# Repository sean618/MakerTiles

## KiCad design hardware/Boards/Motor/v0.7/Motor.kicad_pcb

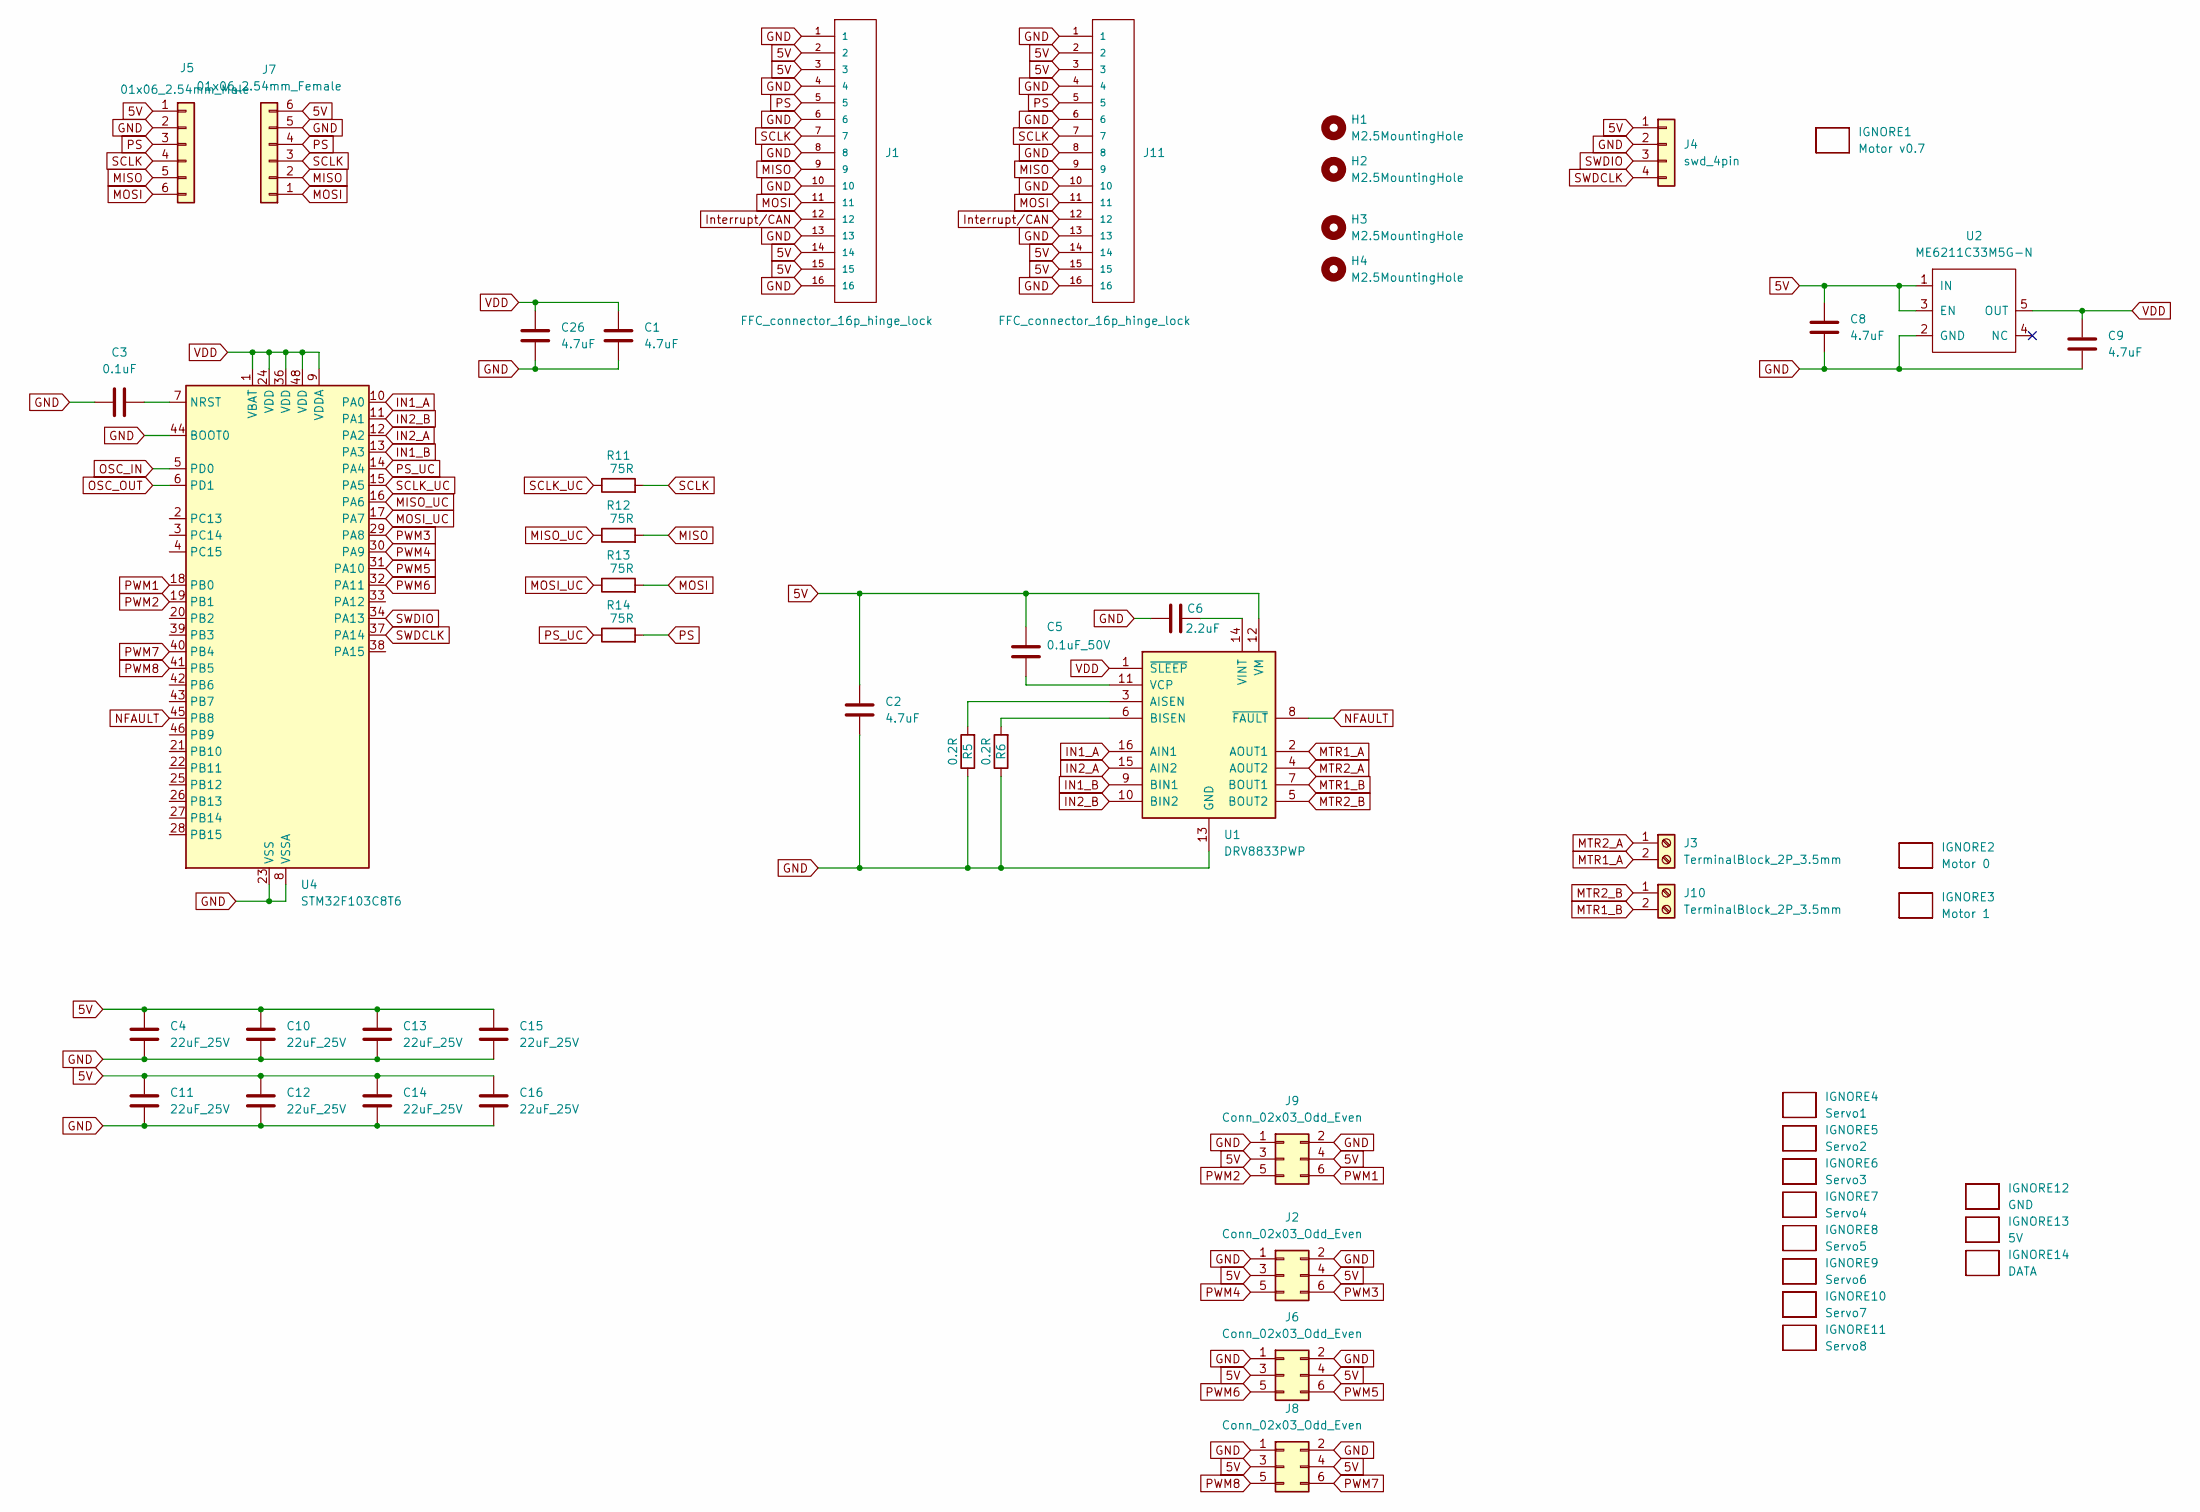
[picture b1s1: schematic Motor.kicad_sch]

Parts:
C1, C2, C8, C9, C26: 4.7uF; C_0402_1005Metric
C3: 0.1uF; C_0402_1005Metric
C4, C10, C11, C12, C13, C14, C15, C16: 22uF_25V; C_0805_2012Metric
C5: 0.1uF_50V; C_0402_1005Metric
C6: 2.2uF; C_0402_1005Metric
H1, H2, H3, H4: M2.5MountingHole; MountingHole_2.7mm_M2.5_ISO7380
IGNORE1: Motor v0.7; BoardText
IGNORE2: Motor 0; BoardText
IGNORE3: Motor 1; BoardText
IGNORE4: Servo1; BoardText
IGNORE5: Servo2; BoardText
IGNORE6: Servo3; BoardText
IGNORE7: Servo4; BoardText
IGNORE8: Servo5; BoardText
IGNORE9: Servo6; BoardText
IGNORE10: Servo7; BoardText
IGNORE11: Servo8; BoardText
IGNORE12: GND; BoardText
IGNORE13: 5V; BoardText
IGNORE14: DATA; BoardText
J1, J11: FFC_connector_16p_hinge_lock
J2, J6, J8, J9: Conn_02x03_Odd_Even; PinHeader_2x03_P2.54mm_Vertical_SMD
J3, J10: TerminalBlock_2P_3.5mm
J4: swd_4pin; swd_header
J5: 01x06_2.54mm_Male
J7: 01x06_2.54mm_Female
R5, R6: 0.2R; R_1210_3225Metric
R11, R12, R13, R14: 75R; R_0402_1005Metric
U1: DRV8833PWP; HTSSOP-16-1EP_4.4x5mm_P0.65mm_EP3.4x5mm_Mask2.46x2.31mm_The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
U2: ME6211C33M5G-N; SOT-23-5
U4: STM32F103C8T6; LQFP-48_7x7mm_P0.5mm

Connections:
5V: C2.1, C4.1, C5.1, C8.1, C10.1, C11.1, C12.1, C13.1, C14.1, C15.1, C16.1, J1.2, J1.3, J1.14, J1.15, J2.3, J2.4, J4.1, J5.1, J6.3, J6.4, J7.6, J8.3, J8.4, J9.3, J9.4, J11.2, J11.3, J11.14, J11.15, U1.12 (VM), U2.1 (IN), U2.3 (EN)
GND: C1.2, C2.2, C3.1, C4.2, C6.1, C8.2, C9.2, C10.2, C11.2, C12.2, C13.2, C14.2, C15.2, C16.2, C26.2, J1.1, J1.4, J1.6, J1.8, J1.10, J1.13, J1.16, J2.1, J2.2, J4.2, J5.2, J6.1, J6.2, J7.5, J8.1, J8.2, J9.1, J9.2, J11.1, J11.4, J11.6, J11.8, J11.10, J11.13, J11.16, R5.1, R6.1, U1.13 (GND), U1.17 (GND), U2.2 (GND), U4.8 (VSSA), U4.23 (VSS), U4.35 (VSS), U4.44 (BOOT0), U4.47 (VSS)
IN1_A: U1.16 (AIN1), U4.10 (PA0)
IN1_B: U1.9 (BIN1), U4.13 (PA3)
IN2_A: U1.15 (AIN2), U4.12 (PA2)
IN2_B: U1.10 (BIN2), U4.11 (PA1)
Interrupt/CAN: J1.12, J11.12
MISO: J1.9, J5.5, J7.2, J11.9, R12.2
MISO_UC: R12.1, U4.16 (PA6)
MOSI: J1.11, J5.6, J7.1, J11.11, R13.2
MOSI_UC: R13.1, U4.17 (PA7)
MTR1_A: J3.2, U1.2 (AOUT1)
MTR1_B: J10.2, U1.7 (BOUT1)
MTR2_A: J3.1, U1.4 (AOUT2)
MTR2_B: J10.1, U1.5 (BOUT2)
NFAULT: U1.8 (~FAULT), U4.45 (PB8)
unnamed: R5.2, U1.3 (AISEN)
unnamed: R6.2, U1.6 (BISEN)
unnamed: C5.2, U1.11 (VCP)
unnamed: C6.2, U1.14 (VINT)
unnamed: C3.2, U4.7 (NRST)
OSC_IN: U4.5 (PD0)
OSC_OUT: U4.6 (PD1)
PS: J1.5, J5.3, J7.4, J11.5, R14.2
PS_UC: R14.1, U4.14 (PA4)
PWM1: J9.6, U4.18 (PB0)
PWM2: J9.5, U4.19 (PB1)
PWM3: J2.6, U4.29 (PA8)
PWM4: J2.5, U4.30 (PA9)
PWM5: J6.6, U4.31 (PA10)
PWM6: J6.5, U4.32 (PA11)
PWM7: J8.6, U4.40 (PB4)
PWM8: J8.5, U4.41 (PB5)
SCLK: J1.7, J5.4, J7.3, J11.7, R11.2
SCLK_UC: R11.1, U4.15 (PA5)
SWDCLK: J4.4, U4.37 (PA14)
SWDIO: J4.3, U4.34 (PA13)
VDD: C1.1, C9.1, C26.1, U1.1 (~SLEEP), U2.5 (OUT), U4.1 (VBAT), U4.9 (VDDA), U4.24 (VDD), U4.36 (VDD), U4.48 (VDD)

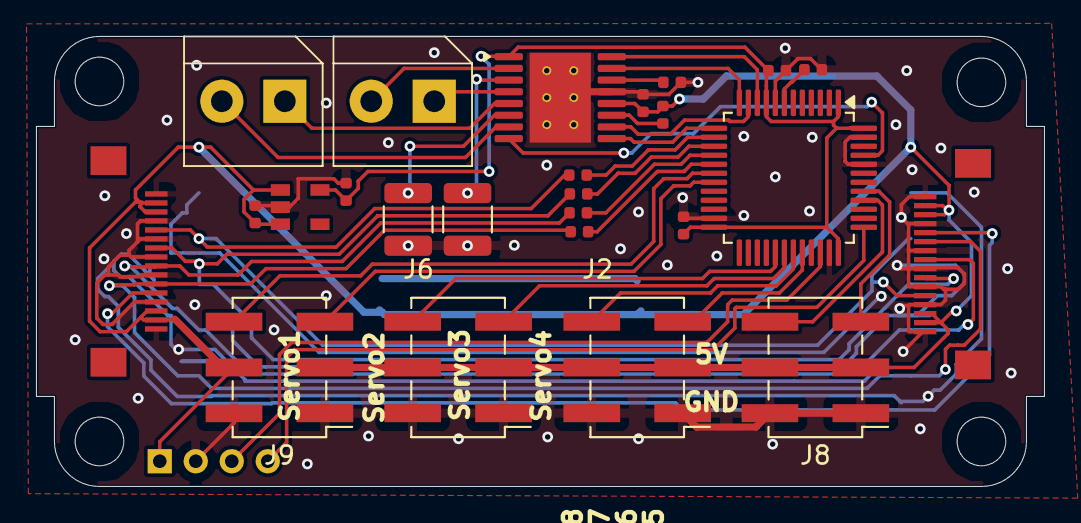
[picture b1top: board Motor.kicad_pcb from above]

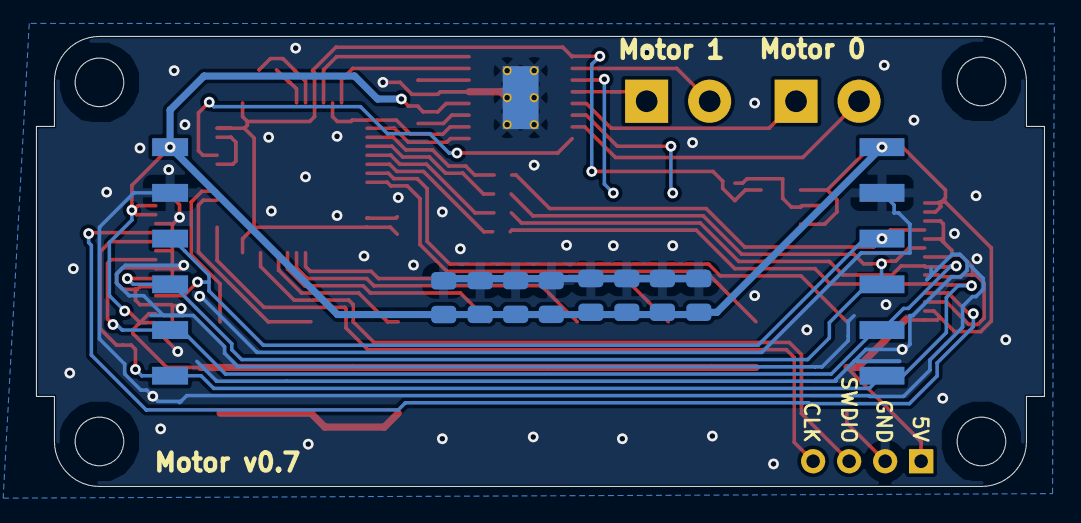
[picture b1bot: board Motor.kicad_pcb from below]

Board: 2 copper layers, 56.0 x 25.0 mm, 54 parts (21 on the bottom side), 36 nets.

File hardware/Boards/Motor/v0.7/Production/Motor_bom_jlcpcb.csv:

Comment,Designator,Footprint,LCSC Part Number
4.7uF,"C9,C1,C2,C26,C8",C_0402_1005Metric,C23733
DRV8833PWP,U1,HTSSOP-16-1EP_4.4x5mm_P0.65mm_EP3.4x5mm_Mask2.46x2.31mm_ThermalVias,C50506
FFC_connector_16p_hinge_lock,"J1,J11",FFC_connector_16p_hinge_lock,C262665
Conn_02x03_Odd_Even,"J2,J8,J6,J9",PinHeader_2x03_P2.54mm_Vertical_SMD,C22438447
0.1uF_50V,C5,C_0402_1005Metric,C77020
75R,"R13,R14,R12,R11",R_0402_1005Metric,C25133
TerminalBlock_2P_3.5mm,"J3,J10",TerminalBlock_2P_3.5mm,C466970
ME6211C33M5G-N,U2,SOT-23-5,C81233
0.1uF,C3,C_0402_1005Metric,C1525
STM32F103C8T6,U4,LQFP-48_7x7mm_P0.5mm,C8734
2.2uF,C6,C_0402_1005Metric,C12530
0.2R,"R5,R6",R_1210_3225Metric,C52362
01x06_2.54mm_Male,J5,01x06_2.54mm_Male,C5242199
22uF_25V,"C15,C10,C12,C4,C14,C13,C11,C16",C_0805_2012Metric,C602037
01x06_2.54mm_Female,J7,01x06_2.54mm_Female,C5142239

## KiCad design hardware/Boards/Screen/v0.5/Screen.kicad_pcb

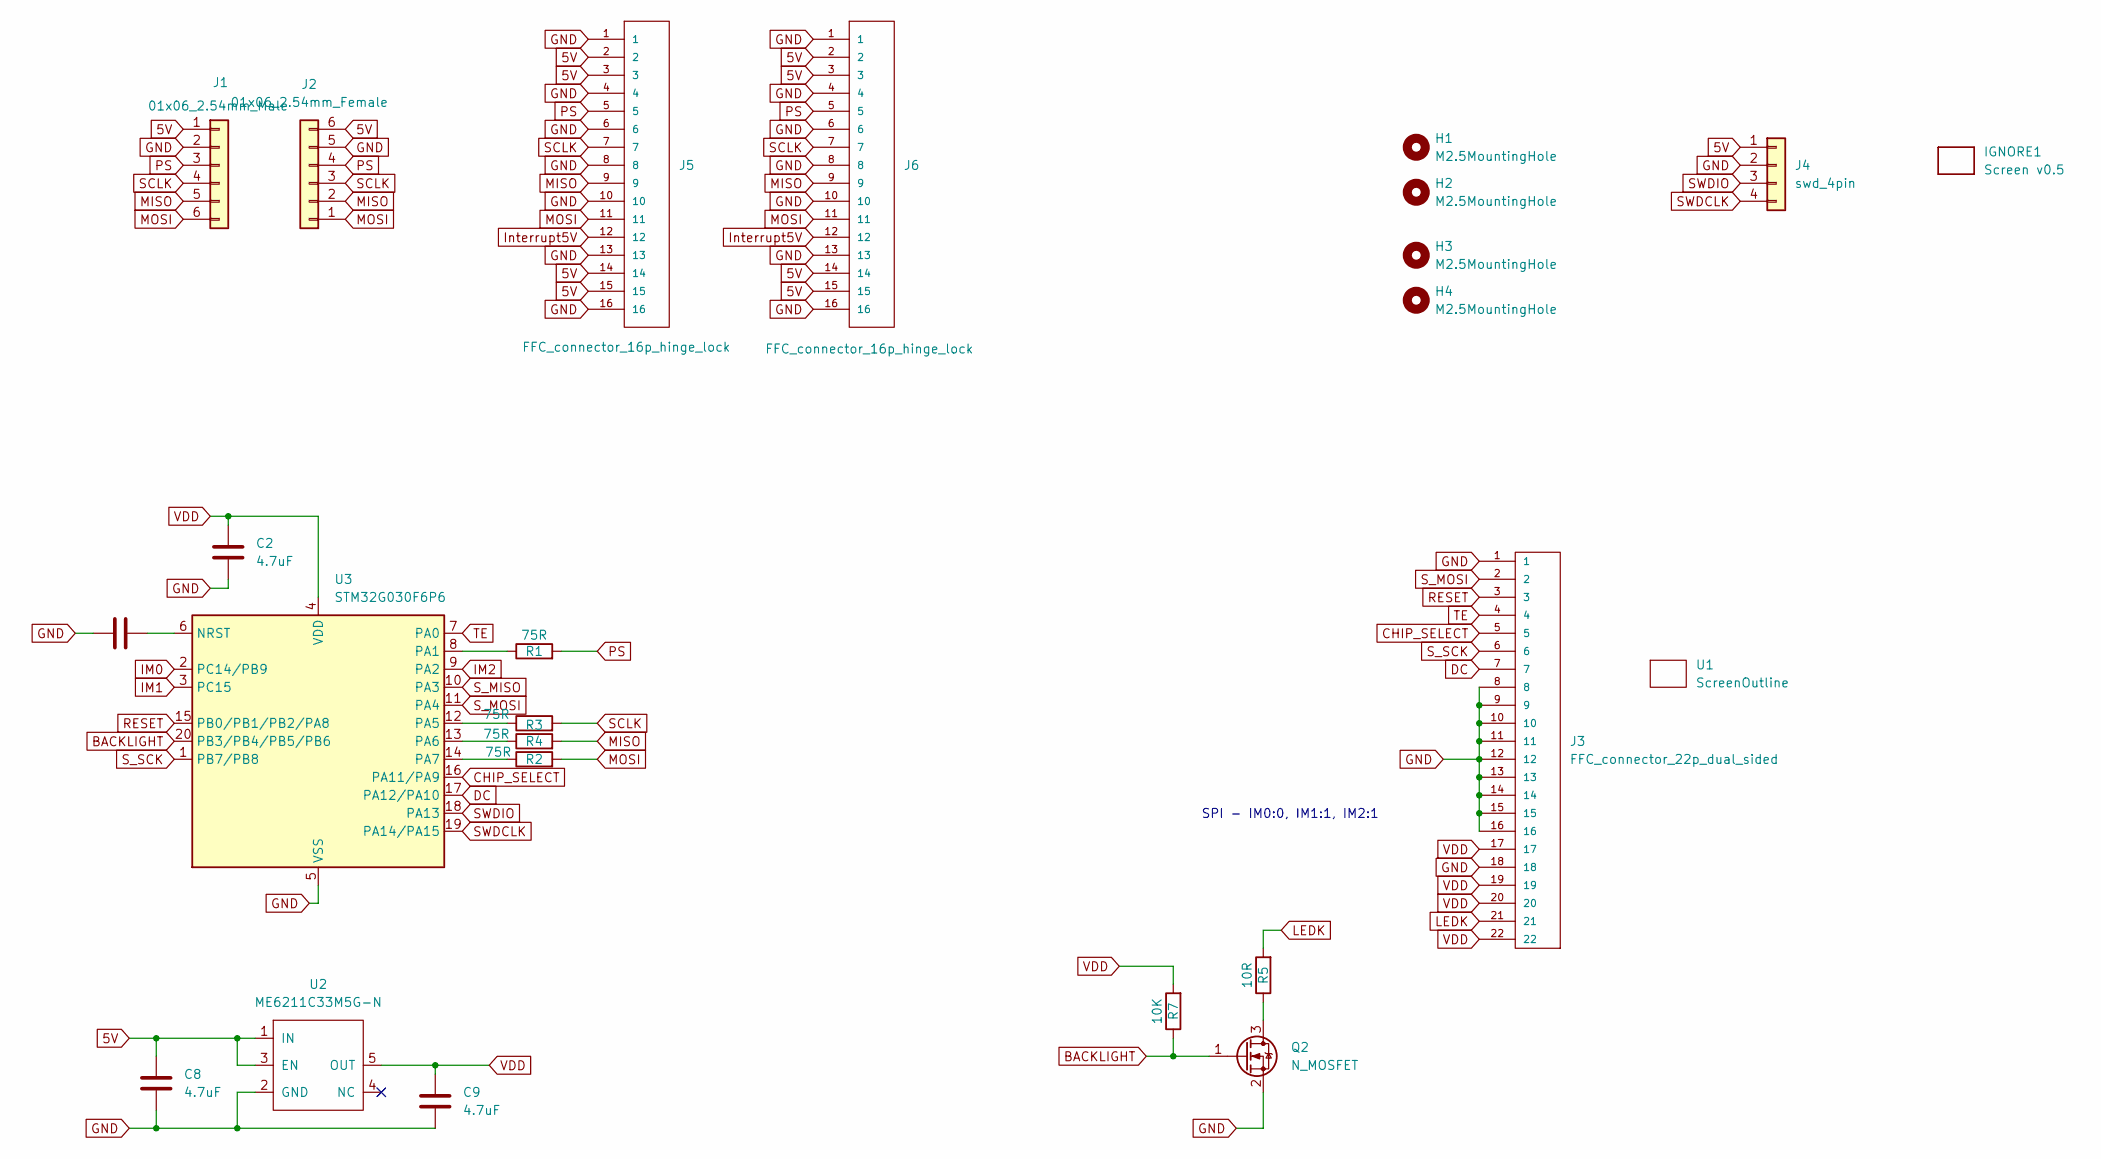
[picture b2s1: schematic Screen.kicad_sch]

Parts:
C1: 0.1uF; C_0402_1005Metric
C2, C8, C9: 4.7uF; C_0402_1005Metric
H1, H2, H3, H4: M2.5MountingHole; MountingHole_2.7mm_M2.5_ISO7380
IGNORE1: Screen v0.5; BoardText
J1: 01x06_2.54mm_Male
J2: 01x06_2.54mm_Female
J3: FFC_connector_22p_dual_sided; FFC_connector_22p_hinge_lock
J4: swd_4pin; swd_header
J5, J6: FFC_connector_16p_hinge_lock
Q2: N_MOSFET; SOT-23
R1, R2, R3, R4: 75R; R_0402_1005Metric
R5: 10R; R_0402_1005Metric
R7: 10K; R_0402_1005Metric
U1: ScreenOutline; 2InchScreen
U2: ME6211C33M5G-N; SOT-23-5
U3: STM32G030F6P6; TSSOP-20_4.4x6.5mm_P0.65mm

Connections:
5V: C8.1, J1.1, J2.6, J4.1, J5.2, J5.3, J5.14, J5.15, J6.2, J6.3, J6.14, J6.15, U2.1 (IN), U2.3 (EN)
BACKLIGHT: Q2.1 (G), R7.1, U3.20 (PB3/PB4/PB5/PB6)
CHIP_SELECT: J3.5, U3.16 (PA11/PA9)
DC: J3.7, U3.17 (PA12/PA10)
GND: C1.2, C2.2, C8.2, C9.2, J1.2, J2.5, J3.1, J3.8, J3.9, J3.10, J3.11, J3.12, J3.13, J3.14, J3.15, J3.16, J3.18, J4.2, J5.1, J5.4, J5.6, J5.8, J5.10, J5.13, J5.16, J6.1, J6.4, J6.6, J6.8, J6.10, J6.13, J6.16, Q2.2 (S), U2.2 (GND), U3.5 (VSS)
IM0: U3.2 (PC14/PB9)
IM1: U3.3 (PC15)
IM2: U3.9 (PA2)
Interrupt5V: J5.12, J6.12
LEDK: J3.21, R5.2
MISO: J1.5, J2.2, J5.9, J6.9, R4.2
MOSI: J1.6, J2.1, J5.11, J6.11, R2.2
unnamed: Q2.3 (D), R5.1
unnamed: C1.1, U3.6 (NRST)
unnamed: R1.1, U3.8 (PA1)
unnamed: R3.1, U3.12 (PA5)
unnamed: R4.1, U3.13 (PA6)
unnamed: R2.1, U3.14 (PA7)
PS: J1.3, J2.4, J5.5, J6.5, R1.2
RESET: J3.3, U3.15 (PB0/PB1/PB2/PA8)
SCLK: J1.4, J2.3, J5.7, J6.7, R3.2
SWDCLK: J4.4, U3.19 (PA14/PA15)
SWDIO: J4.3, U3.18 (PA13)
S_MISO: U3.10 (PA3)
S_MOSI: J3.2, U3.11 (PA4)
S_SCK: J3.6, U3.1 (PB7/PB8)
TE: J3.4, U3.7 (PA0)
VDD: C2.1, C9.1, J3.17, J3.19, J3.20, J3.22, R7.2, U2.5 (OUT), U3.4 (VDD)

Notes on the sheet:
SPI - IM0:0, IM1:1, IM2:1

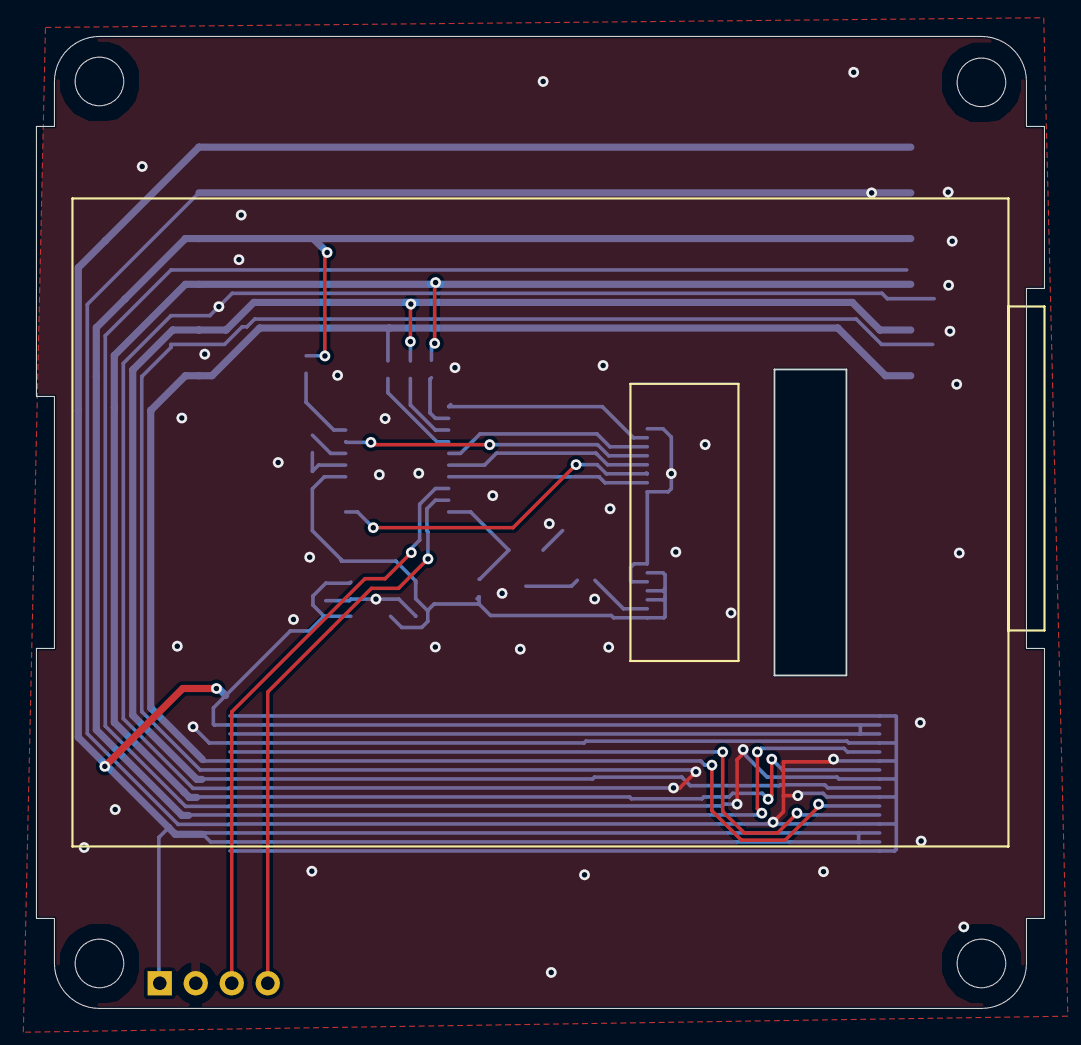
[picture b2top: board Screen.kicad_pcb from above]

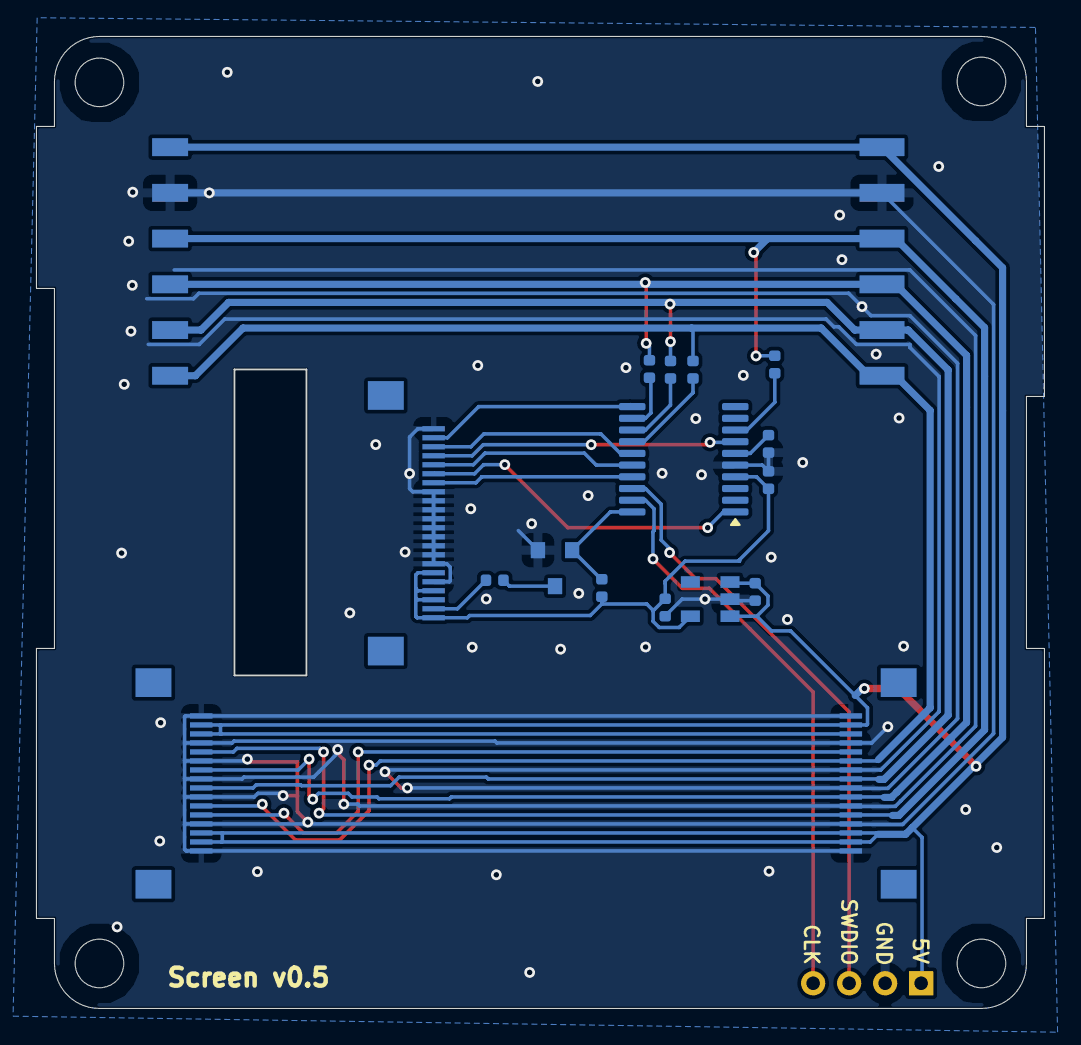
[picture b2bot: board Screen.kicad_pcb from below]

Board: 2 copper layers, 56.0 x 54.0 mm, 25 parts (18 on the bottom side), 24 nets.

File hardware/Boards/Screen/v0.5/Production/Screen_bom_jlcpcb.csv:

Comment,Designator,Footprint,LCSC Part Number
4.7uF,"C9,C8,C2",C_0402_1005Metric,C23733
FFC_connector_22p_dual_sided,J3,FFC_connector_22p_hinge_lock,C557729
FFC_connector_16p_hinge_lock,"J5,J6",FFC_connector_16p_hinge_lock,C262665
ME6211C33M5G-N,U2,SOT-23-5,C81233
75R,"R2,R3,R4,R1",R_0402_1005Metric,C25133
STM32G030F6P6,U3,TSSOP-20_4.4x6.5mm_P0.65mm,C529330
N_MOSFET,Q2,SOT-23,C8545
0.1uF,C1,C_0402_1005Metric,C1525
01x06_2.54mm_Female,J2,01x06_2.54mm_Female,C5142239
10R,R5,R_0402_1005Metric,C25077
01x06_2.54mm_Male,J1,01x06_2.54mm_Male,C5242199
10K,R7,R_0402_1005Metric,C25744

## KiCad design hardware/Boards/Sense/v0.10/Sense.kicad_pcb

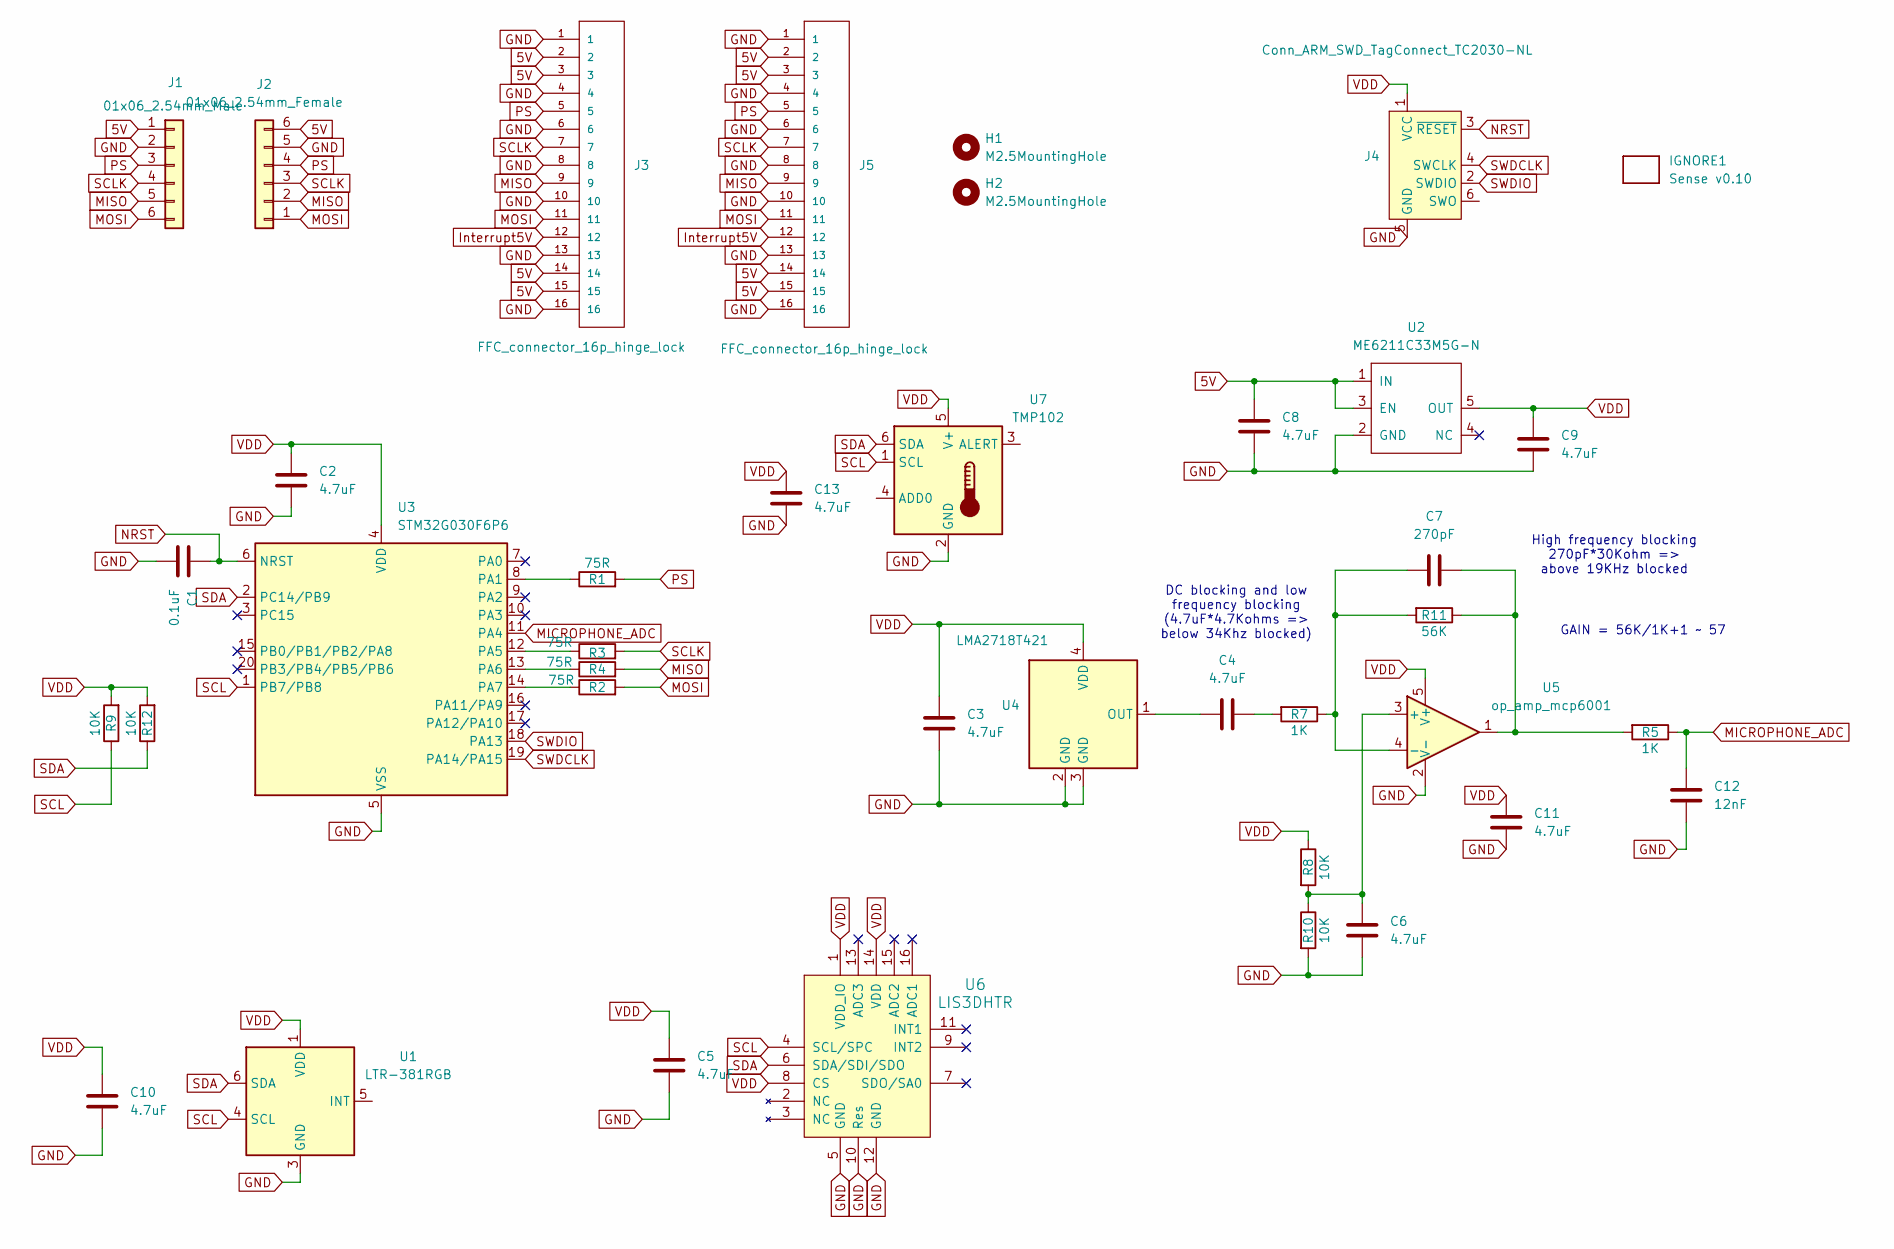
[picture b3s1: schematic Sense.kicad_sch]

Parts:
C1: 0.1uF; C_0402_1005Metric
C2, C3, C4, C5, C6, C8, C9, C10, C11, C13: 4.7uF; C_0402_1005Metric
C7: 270pF; C_0402_1005Metric
C12: 12nF; C_0402_1005Metric
H1, H2: M2.5MountingHole; MountingHole_2.7mm_M2.5_ISO7380
IGNORE1: Sense v0.10; BoardText
J1: 01x06_2.54mm_Male
J2: 01x06_2.54mm_Female
J3, J5: FFC_connector_16p_hinge_lock
J4: Conn_ARM_SWD_TagConnect_TC2030-NL; Tag-Connect_TC2030-IDC-NL_2x03_P1.27mm_Vertical
R1, R2, R3, R4: 75R; R_0402_1005Metric
R5, R7: 1K; R_0402_1005Metric
R8, R9, R10, R12: 10K; R_0402_1005Metric
R11: 56K; R_0402_1005Metric
U1: LTR-381RGB
U2: ME6211C33M5G-N; SOT-23-5
U3: STM32G030F6P6; TSSOP-20_4.4x6.5mm_P0.65mm
U4: LMA2718T421; SMD-4P-2.8x1.9mm
U5: op_amp_mcp6001; SOT-23-5
U6: LIS3DHTR; LGA-16_3x3mm_P0.5mm_LayoutBorder3x5y; Manufacturer_Part_Number LIS3DHTR
U7: TMP102; SOT-563

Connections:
5V: C8.1, J1.1, J2.6, J3.2, J3.3, J3.14, J3.15, J5.2, J5.3, J5.14, J5.15, U2.1 (IN), U2.3 (EN)
GND: C1.2, C2.2, C3.2, C5.2, C6.1, C8.2, C9.2, C10.2, C11.2, C12.1, C13.2, J1.2, J2.5, J3.1, J3.4, J3.6, J3.8, J3.10, J3.13, J3.16, J4.5 (GND), J5.1, J5.4, J5.6, J5.8, J5.10, J5.13, J5.16, R10.2, U1.3 (GND), U2.2 (GND), U3.5 (VSS), U4.2 (GND), U4.3 (GND), U5.2 (V-), U6.5 (GND), U6.10 (Res), U6.12 (GND), U7.2 (GND)
Interrupt5V: J3.12, J5.12
MICROPHONE_ADC: C12.2, R5.1, U3.11 (PA4)
MISO: J1.5, J2.2, J3.9, J5.9, R4.2
MOSI: J1.6, J2.1, J3.11, J5.11, R2.2
NRST: C1.1, J4.3 (~RESET), U3.6 (NRST)
unnamed: C4.2, R7.2
unnamed: C7.2, R5.2, R11.1, U5.1
unnamed: R1.1, U3.8 (PA1)
unnamed: R3.1, U3.12 (PA5)
unnamed: R4.1, U3.13 (PA6)
unnamed: R2.1, U3.14 (PA7)
unnamed: C4.1, U4.1 (OUT)
unnamed: C6.2, R8.2, R10.1, U5.3 (+)
unnamed: C7.1, R7.1, R11.2, U5.4 (-)
PS: J1.3, J2.4, J3.5, J5.5, R1.2
SCL: R9.1, U1.4 (SCL), U3.1 (PB7/PB8), U6.4 (SCL/SPC), U7.1 (SCL)
SCLK: J1.4, J2.3, J3.7, J5.7, R3.2
SDA: R12.1, U1.6 (SDA), U3.2 (PC14/PB9), U6.6 (SDA/SDI/SDO), U7.6 (SDA)
SWDCLK: J4.4 (SWCLK), U3.19 (PA14/PA15)
SWDIO: J4.2 (SWDIO), U3.18 (PA13)
VDD: C2.1, C3.1, C5.1, C9.1, C10.1, C11.1, C13.1, J4.1 (VCC), R8.1, R9.2, R12.2, U1.1 (VDD), U2.5 (OUT), U3.4 (VDD), U4.4 (VDD), U5.5 (V+), U6.1 (VDD_IO), U6.8 (CS), U6.14 (VDD), U7.5 (V+)

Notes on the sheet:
GAIN = 56K/1K+1 ~ 57
High frequency blocking 270pF*30Kohm => above 19KHz blocked
DC blocking and low frequency blocking (4.7uF*4.7Kohms => below 34Khz blocked)

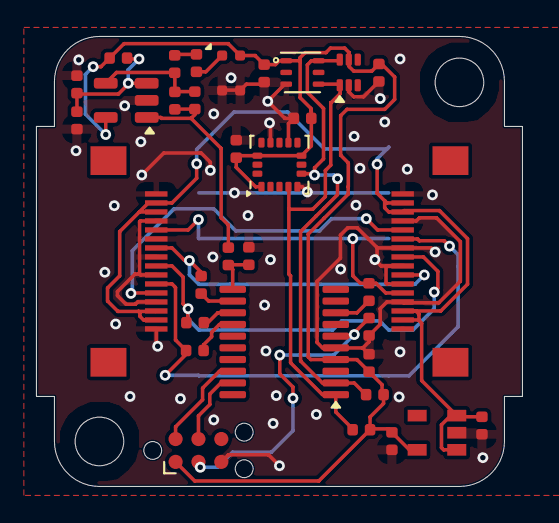
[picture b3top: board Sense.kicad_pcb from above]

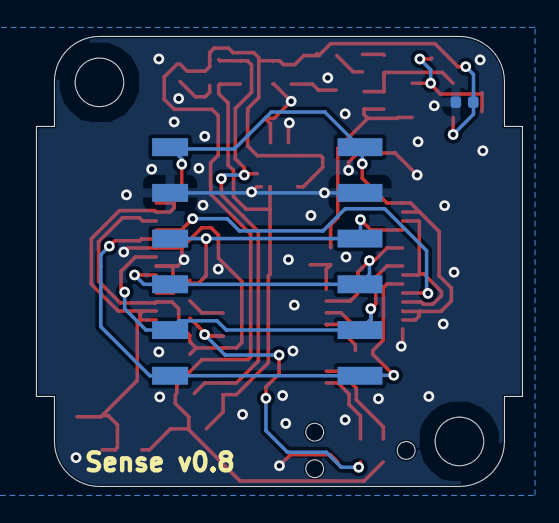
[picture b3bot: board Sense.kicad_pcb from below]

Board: 2 copper layers, 27.0 x 25.0 mm, 39 parts (3 on the bottom side), 23 nets.

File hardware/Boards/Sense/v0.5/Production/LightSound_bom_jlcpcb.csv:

Comment,Designator,Footprint,LCSC Part Number
4.7uF,"C9,C8,C2,C3",C_0402_1005Metric,C23733
FFC_connector_16p_hinge_lock,"J3,J5",FFC_connector_16p_hinge_lock,C262665
10K,"R5,R6",R_0402_1005Metric,C25744
ME6211C33M5G-N,U2,SOT-23-5,C81233
75R,"R2,R3,R4,R1",R_0402_1005Metric,C25133
STM32G030F6P6,U3,TSSOP-20_4.4x6.5mm_P0.65mm,C529330
WMM7027ATSN1-4/TR,U4,LGA-4,C2931973
0.1uF,C1,C_0402_1005Metric,C1525
LTR-381RGB,U1,LTR-381RGB,C2944020
01x06_2.54mm_Male,J1,01x06_2.54mm_Male,C5242199
01x06_2.54mm_Female,J2,01x06_2.54mm_Female,C5142239

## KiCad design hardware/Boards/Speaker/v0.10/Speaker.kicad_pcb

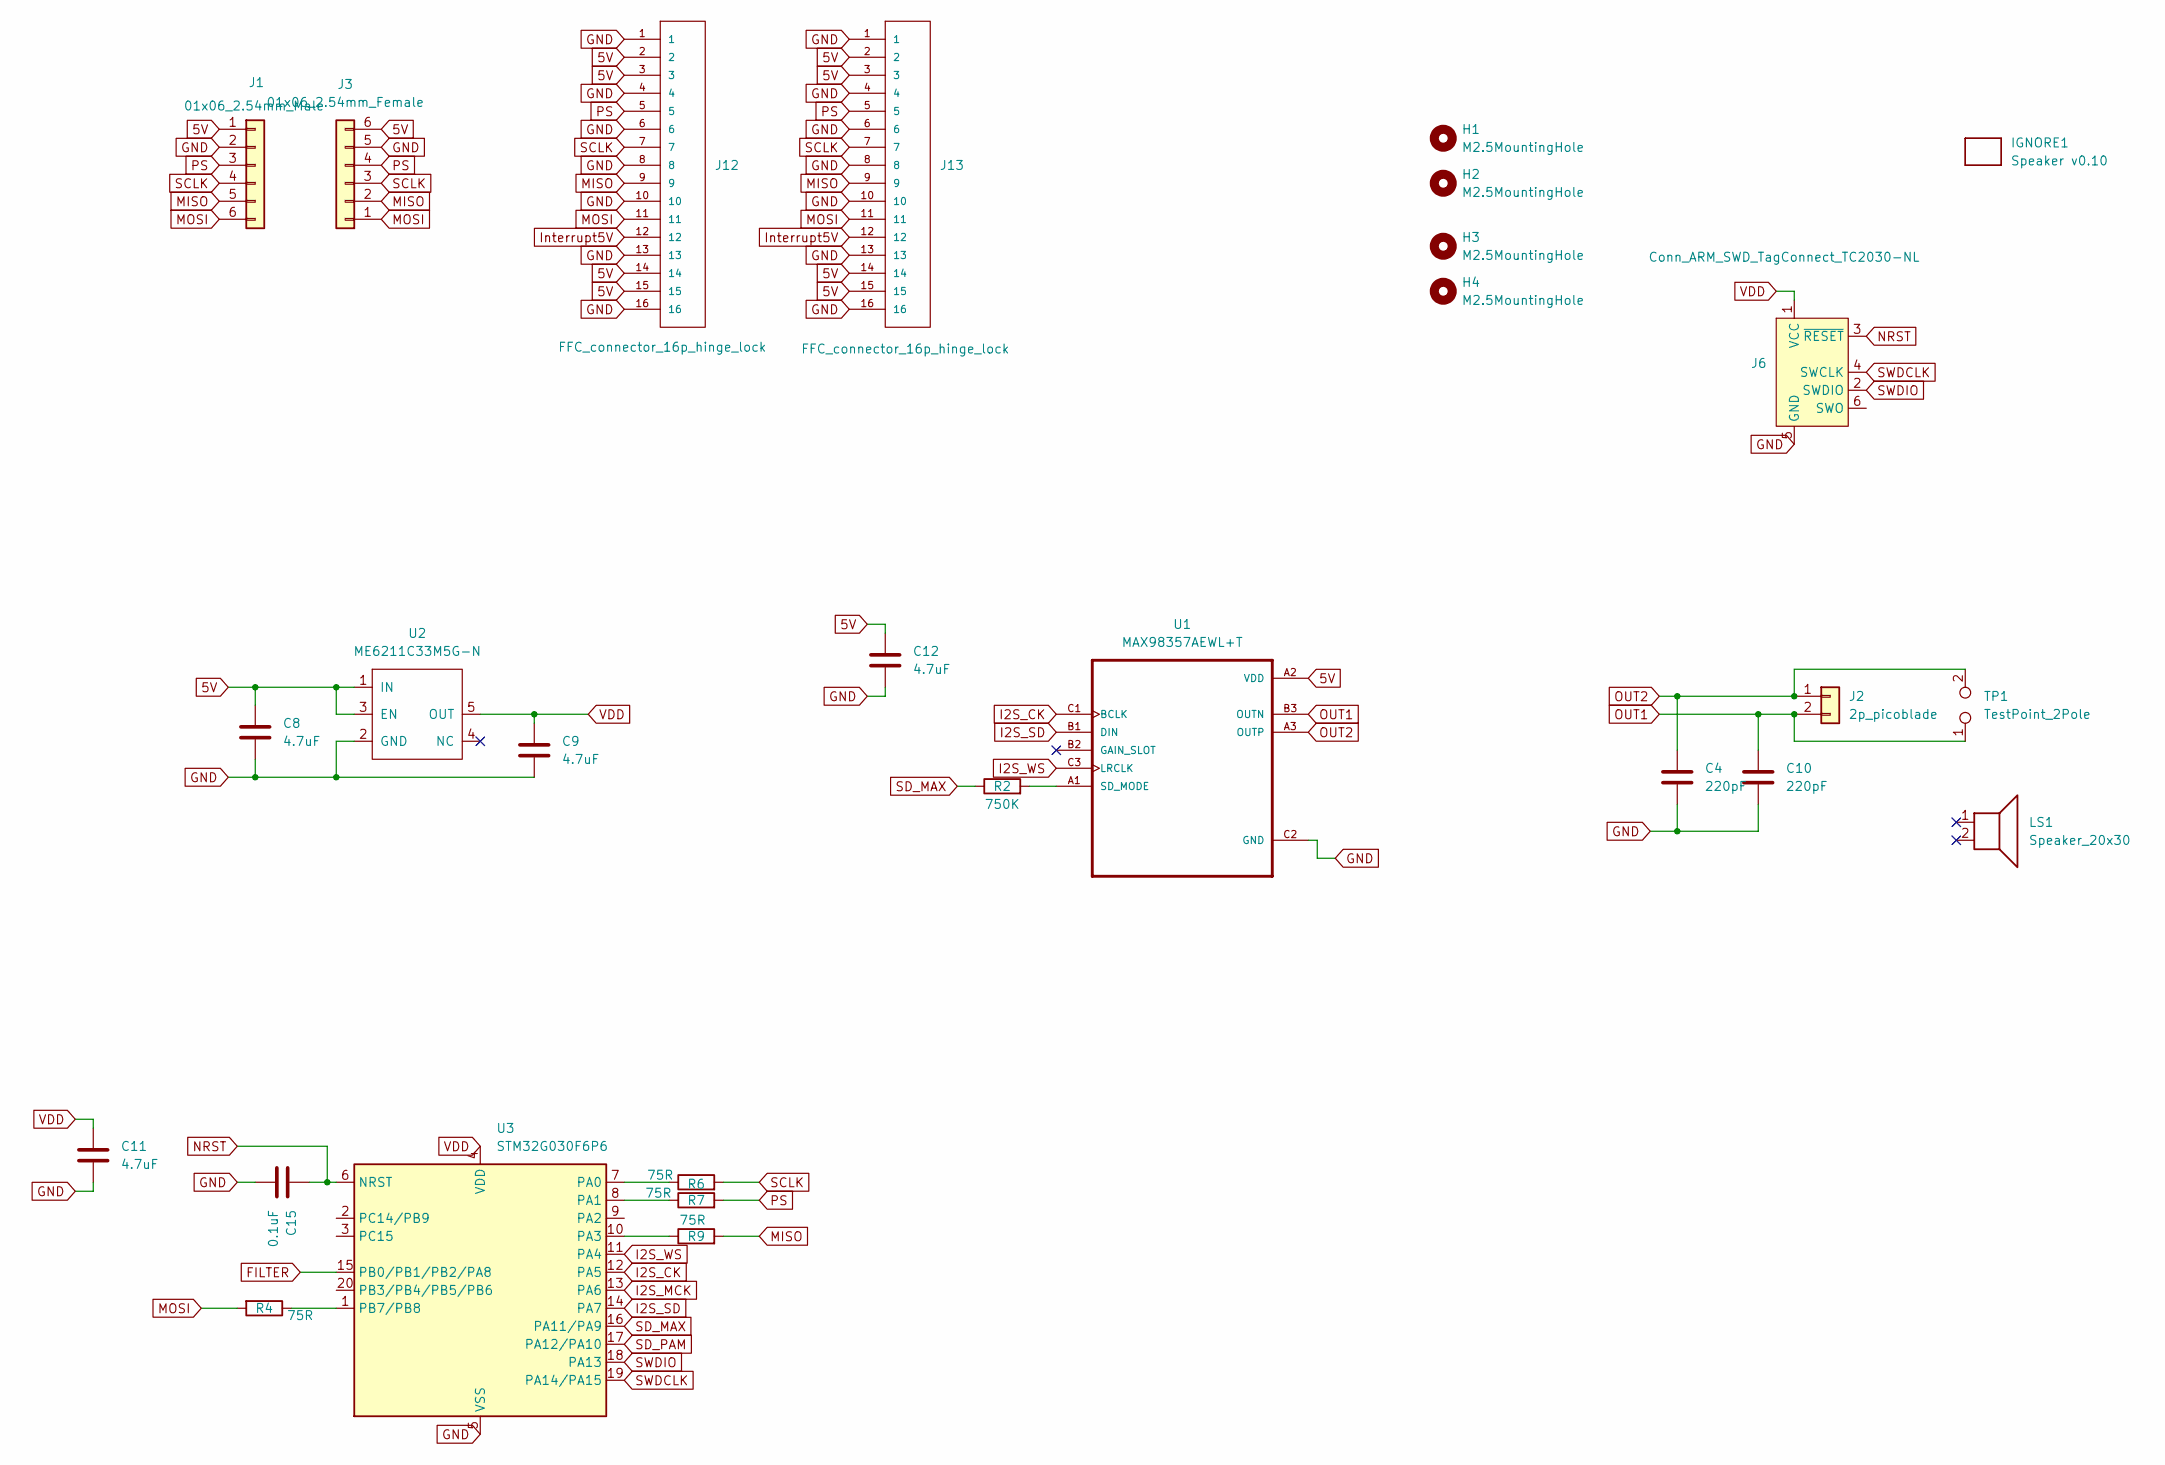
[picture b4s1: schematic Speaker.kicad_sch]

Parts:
C4, C10: 220pF; C_0402_1005Metric
C8, C9, C11, C12: 4.7uF; C_0402_1005Metric
C15: 0.1uF; C_0402_1005Metric
H1, H2, H3, H4: M2.5MountingHole; MountingHole_2.7mm_M2.5_ISO7380
IGNORE1: Speaker v0.10; BoardText
J1: 01x06_2.54mm_Male
J2: 2p_picoblade; Molex_PicoBlade_53261-0271_1x02-1MP_P1.25mm_Horizontal
J3: 01x06_2.54mm_Female
J6: Conn_ARM_SWD_TagConnect_TC2030-NL; Tag-Connect_TC2030-IDC-NL_2x03_P1.27mm_Vertical
J12, J13: FFC_connector_16p_hinge_lock
LS1: Speaker_20x30
R2: 750K; R_0402_1005Metric
R4, R6, R7, R9: 75R; R_0402_1005Metric
TP1: TestPoint_2Pole; TestPoint_2Pads_Pitch2.54mm_Drill0.8mm
U1: MAX98357AEWL+T; WLP-9_1.448x1.468mm_Layout3x3_P0.4mm_Ball0.27mm_Pad0.25mm
U2: ME6211C33M5G-N; SOT-23-5
U3: STM32G030F6P6; TSSOP-20_4.4x6.5mm_P0.65mm

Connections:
5V: C8.1, C12.1, J1.1, J3.6, J12.2, J12.3, J12.14, J12.15, J13.2, J13.3, J13.14, J13.15, U1.A2 (VDD), U2.1 (IN), U2.3 (EN)
FILTER: U3.15 (PB0/PB1/PB2/PA8)
GND: C4.2, C8.2, C9.2, C10.2, C11.2, C12.2, C15.2, J1.2, J3.5, J6.5 (GND), J12.1, J12.4, J12.6, J12.8, J12.10, J12.13, J12.16, J13.1, J13.4, J13.6, J13.8, J13.10, J13.13, J13.16, U1.C2 (GND), U2.2 (GND), U3.5 (VSS)
I2S_CK: U1.C1 (BCLK), U3.12 (PA5)
I2S_MCK: U3.13 (PA6)
I2S_SD: U1.B1 (DIN), U3.14 (PA7)
I2S_WS: U1.C3 (LRCLK), U3.11 (PA4)
Interrupt5V: J12.12, J13.12
MISO: J1.5, J3.2, J12.9, J13.9, R9.2
MOSI: J1.6, J3.1, J12.11, J13.11, R4.2
NRST: C15.1, J6.3 (~RESET), U3.6 (NRST)
unnamed: R2.2, U1.A1 (SD_MODE)
unnamed: R6.1, U3.7 (PA0)
unnamed: R7.1, U3.8 (PA1)
unnamed: R9.1, U3.10 (PA3)
unnamed: R4.1, U3.1 (PB7/PB8)
OUT1: C10.1, J2.2, TP1.1, U1.B3 (OUTN)
OUT2: C4.1, J2.1, TP1.2, U1.A3 (OUTP)
PS: J1.3, J3.4, J12.5, J13.5, R7.2
SCLK: J1.4, J3.3, J12.7, J13.7, R6.2
SD_MAX: R2.1, U3.16 (PA11/PA9)
SD_PAM: U3.17 (PA12/PA10)
SWDCLK: J6.4 (SWCLK), U3.19 (PA14/PA15)
SWDIO: J6.2 (SWDIO), U3.18 (PA13)
VDD: C9.1, C11.1, J6.1 (VCC), U2.5 (OUT), U3.4 (VDD)
